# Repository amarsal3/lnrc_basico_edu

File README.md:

# lnrc_basico_edu
lnrc_basico_edu es un proyecto de la liga nacional de robotica (lnrc.es) que tiene como objetivo proporcionar un primer contacto con la robótica. 

Básicamente se trata de un robot educativo con el que empezar a trabajar los conceptos básicos de programación dentro de un marco simple y amigable.

El proyecto se divide en la parte física del robot (estructura diseñada en 3D y placa de control) y la capa de programación, que proporciona los bloques necesarios para dar instrucciones al robot de forma sencilla.

Puedes consultar detalles del robot, vídeos y mucha más información en el sitio de la liga dedicado a este proyecto http://lnrc.es/contenido.jsp?idContenido=robotmania.

## Licencia

Todos estos productos están liberados mediante [Creative Commons Attribution-ShareAlike 4.0 International License](http://creativecommons.org/licenses/by-sa/4.0/).  

_All these products are released under [Creative Commons Attribution-ShareAlike 4.0 International License](http://creativecommons.org/licenses/by-sa/4.0/)._

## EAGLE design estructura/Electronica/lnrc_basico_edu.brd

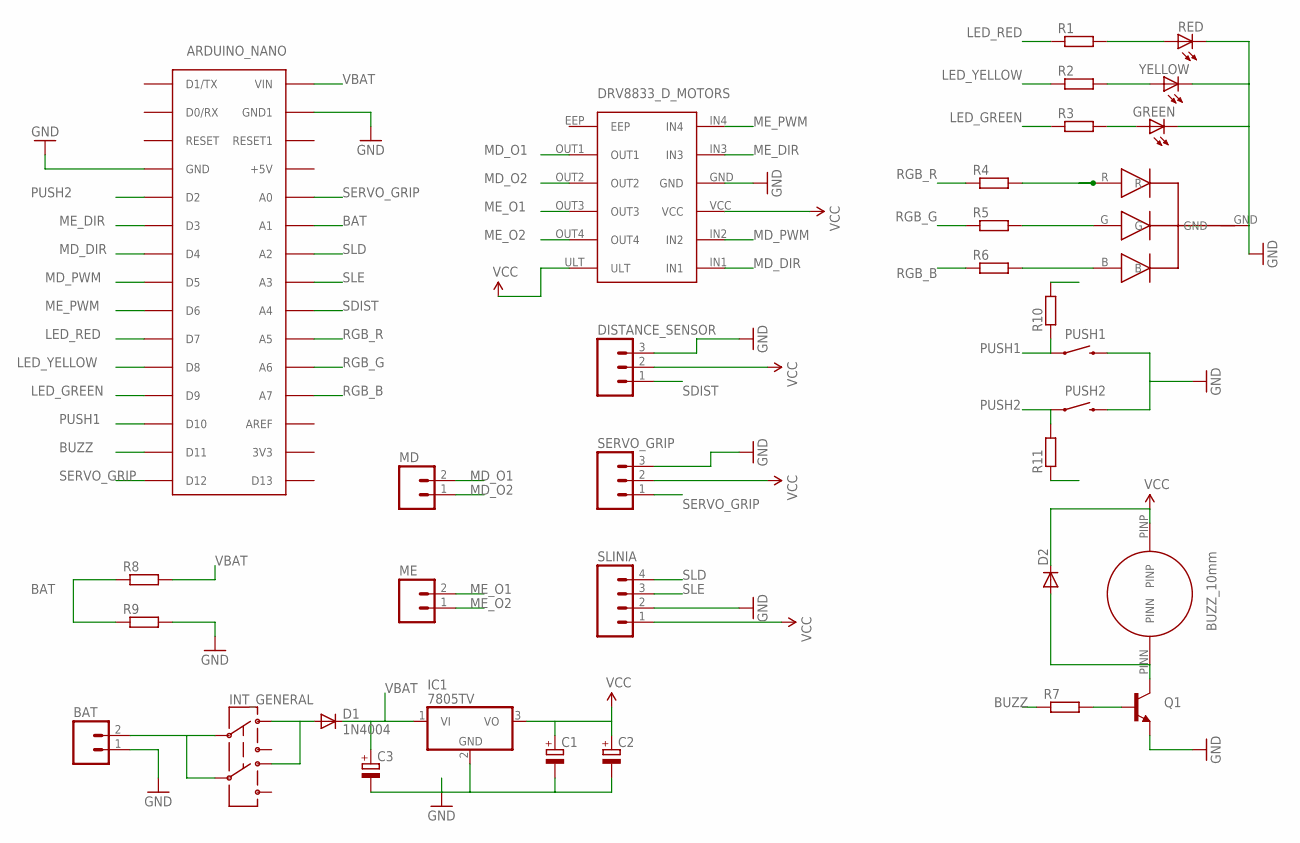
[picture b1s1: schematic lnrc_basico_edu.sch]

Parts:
ARDUINO_NANO: ARDUINONANO; PDIP-32
BAT: M02LOCK_LONGPADS; 1X02_LOCK_LONGPADS
C1, C2, C3: CPOL-EUE2.5-6; E2,5-6
D1: 1N4004; DO41-10
D2: DIODE1N4148; DIODE-1N4148
DISTANCE_SENSOR: M03LONGPADS; 1X03_LONGPADS
DRV8833_D_MOTORS: DRV8833_BREAKOUT
GREEN: LED3MM
IC1: 7805TV; TO220V
INT_GENERAL: AYZ0202_TH
MD: M02; 02P
ME: M02; 02P
PUSH1, PUSH2: SWITCH-MOMENTARY-2PTH; TACTILE-PTH
Q1: TRANSISTOR_NPNBC547; TO-92-AMMO
R1, R2, R3, R4, R5, R6, R7, R8, R9, R10, R11: R-EU_0309_10; 0309/10
RED: LED3MM
SERVO_GRIP: M03LONGPADS; 1X03_LONGPADS
SLINIA: M04LONGPADS; 1X04_LONGPADS
U$1: BUZZ_10MM
U$2: LED_RGB_COMCATH; LED_RGB_COMMCATH
YELLOW: LED3MM

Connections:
BAT: ARDUINO_NANO.A1, R8.1, R9.1
BUZZ: ARDUINO_NANO.D11, R7.1
GND: ARDUINO_NANO.GND, ARDUINO_NANO.GND1, BAT.1, C1.-, C2.-, C3.-, DISTANCE_SENSOR.3, DRV8833_D_MOTORS.GND, GREEN.K (C), IC1.2 (GND), PUSH1.3 (2), PUSH2.3 (2), Q1.3 (E), R9.2, RED.K (C), SERVO_GRIP.3, SLINIA.2, U$2.GND, YELLOW.K (C)
LED_GREEN: ARDUINO_NANO.D9, R3.1
LED_RED: ARDUINO_NANO.D7, R1.1
LED_YELLOW: ARDUINO_NANO.D8, R2.1
MD_DIR: ARDUINO_NANO.D4, DRV8833_D_MOTORS.IN1
MD_O1: DRV8833_D_MOTORS.OUT1, MD.2
MD_O2: DRV8833_D_MOTORS.OUT2, MD.1
MD_PWM: ARDUINO_NANO.D5, DRV8833_D_MOTORS.IN2
ME_DIR: ARDUINO_NANO.D3, DRV8833_D_MOTORS.IN3
ME_O1: DRV8833_D_MOTORS.OUT3, ME.2
ME_O2: DRV8833_D_MOTORS.OUT4, ME.1
ME_PWM: ARDUINO_NANO.D6, DRV8833_D_MOTORS.IN4
unnamed: BAT.2, INT_GENERAL.C1, INT_GENERAL.C2
unnamed: D1.A, INT_GENERAL.D1, INT_GENERAL.D2
unnamed: R1.2, RED.A
unnamed: R2.2, YELLOW.A
unnamed: GREEN.A, R3.2
unnamed: R4.2, U$2.R
unnamed: R5.2, U$2.G
unnamed: R6.2, U$2.B
unnamed: Q1.2 (B), R7.2
unnamed: D2.A, Q1.1 (C), U$1.PINN
PUSH1: ARDUINO_NANO.D10, PUSH1.1, R10.1
PUSH2: ARDUINO_NANO.D2, PUSH2.1, R11.2
RGB_B: ARDUINO_NANO.A7, R6.1
RGB_G: ARDUINO_NANO.A6, R5.1
RGB_R: ARDUINO_NANO.A5, R4.1
SDIST: ARDUINO_NANO.A4, DISTANCE_SENSOR.1
SERVO_GRIP: ARDUINO_NANO.A0, ARDUINO_NANO.D12, SERVO_GRIP.1
SLD: ARDUINO_NANO.A2, SLINIA.4
SLE: ARDUINO_NANO.A3, SLINIA.3
VBAT: ARDUINO_NANO.VIN, C3.+, D1.C, IC1.1 (VI), R8.2
VCC: C1.+, C2.+, D2.C, DISTANCE_SENSOR.2, DRV8833_D_MOTORS.ULT, DRV8833_D_MOTORS.VCC, IC1.3 (VO), R10.2, R11.1, SERVO_GRIP.2, SLINIA.1, U$1.PINP

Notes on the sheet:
ARDUINO_NANO

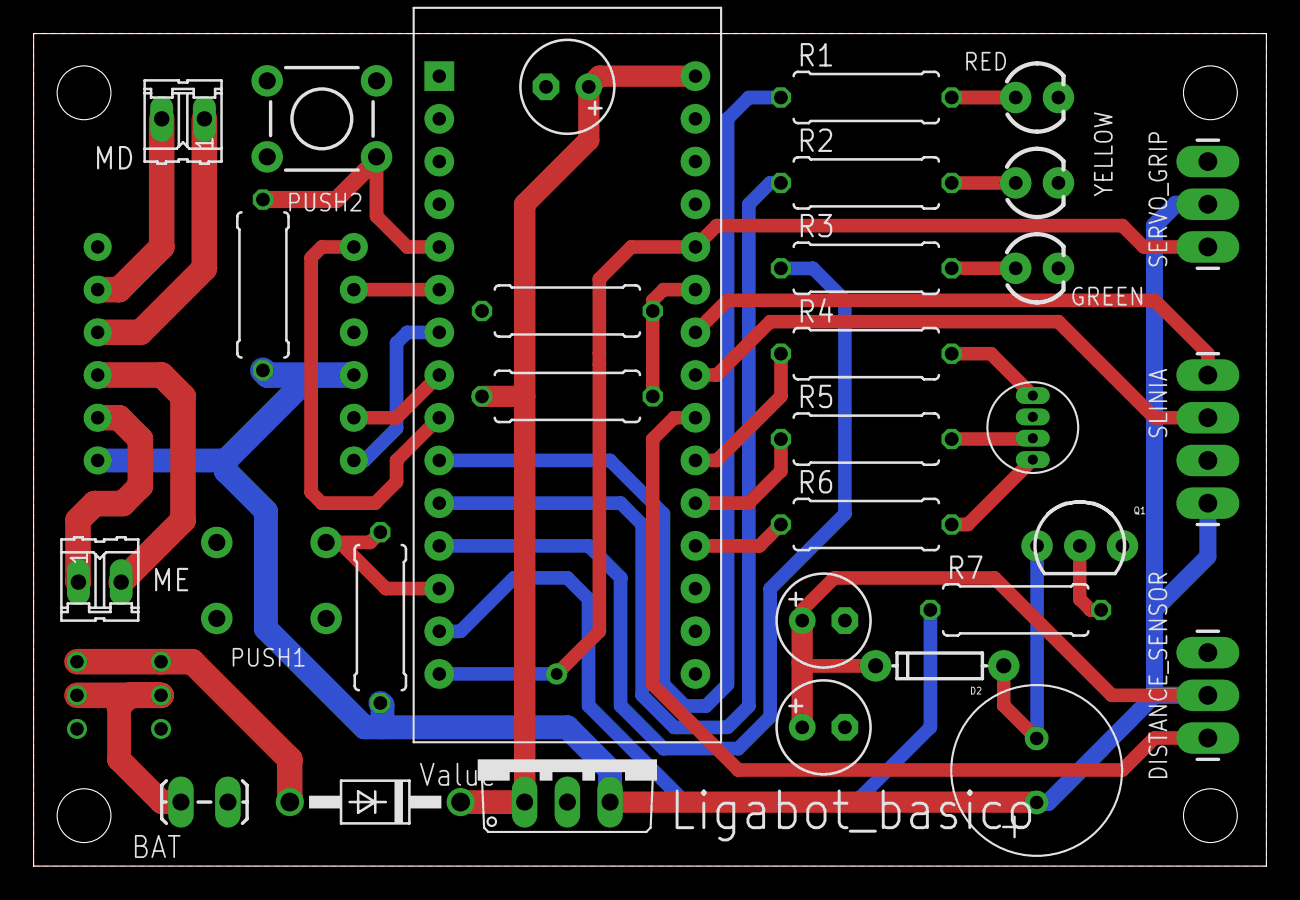
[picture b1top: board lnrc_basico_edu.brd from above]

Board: 2 copper layers, 73.3 x 49.5 mm, 34 parts (1 on the bottom side), 35 nets.

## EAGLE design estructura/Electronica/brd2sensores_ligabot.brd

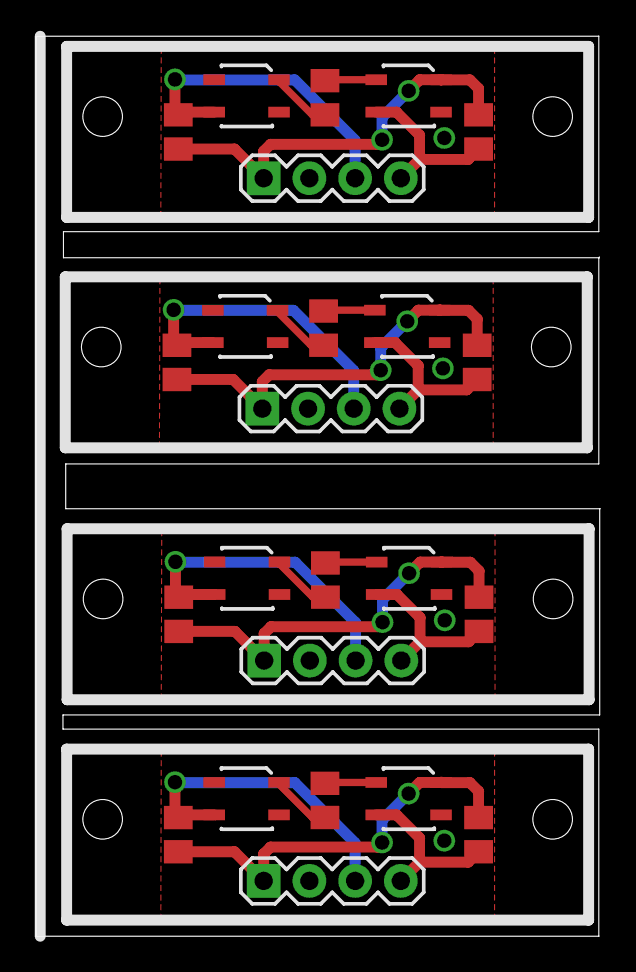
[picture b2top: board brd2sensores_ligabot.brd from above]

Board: 2 copper layers, 31.3 x 50.0 mm, 24 parts (0 on the bottom side), 24 nets.

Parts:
JP2, JP5, JP6, JP7: 1X04
R6, R18, R19, R20, R23, R24: M0805
R21, R22: 47k; M0805
RP1, RP2, RP4: M0805
RP3: 220R; M0805
U$4, U$5, U$6, U$7, U$8, U$9, U$10, U$11: QRE1113

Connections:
GNDS1: JP2.2, U$4.2, U$4.4, U$5.4
GNDS2: JP5.2, U$6.4, U$7.2, U$7.4
GNDS3: JP6.2, U$8.4, U$9.2, U$9.4
GNDS4: JP7.2, U$10.4, U$11.2, U$11.4
unnamed: RP2.2, U$7.1
unnamed: RP1.2, U$4.1
unnamed: RP1.1, U$5.2
unnamed: RP2.1, U$6.2
unnamed: RP3.2, U$9.1
unnamed: RP3.1, U$8.2
unnamed: RP4.2, U$11.1
unnamed: RP4.1, U$10.2
S1: JP2.4, R6.1, U$5.3
S2: JP2.3, R18.1, U$4.3
S3: JP5.4, R19.1, U$6.3
S4: JP5.3, R20.1, U$7.3
S5: JP6.4, R21.1, U$8.3
S6: JP6.3, R22.1, U$9.3
S7: JP7.4, R23.1, U$10.3
S8: JP7.3, R24.1, U$11.3
VCCS1: JP2.1, R6.2, R18.2, U$5.1
VCCS2: JP5.1, R19.2, R20.2, U$6.1
VCCS3: JP6.1, R21.2, R22.2, U$8.1
VCCS4: JP7.1, R23.2, R24.2, U$10.1

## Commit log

2017-12-14 Create Nota_piezas_3D
2017-12-14 Create Nota_electronica
2017-12-14 Update Nota_piezas_3D
2017-12-14 Create Nota_programacion
2017-12-14 Update Nota_programacion

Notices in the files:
parts and their libraries:
SparkFun: Licensing: CC v3.0 Share-Alike You are welcome to use this library for commercial purposes.
SparkFun-Electromechanical: Licensing: Creative Commons ShareAlike 4.0 International - https://creativecommons.org/licenses/by-sa/4.0
